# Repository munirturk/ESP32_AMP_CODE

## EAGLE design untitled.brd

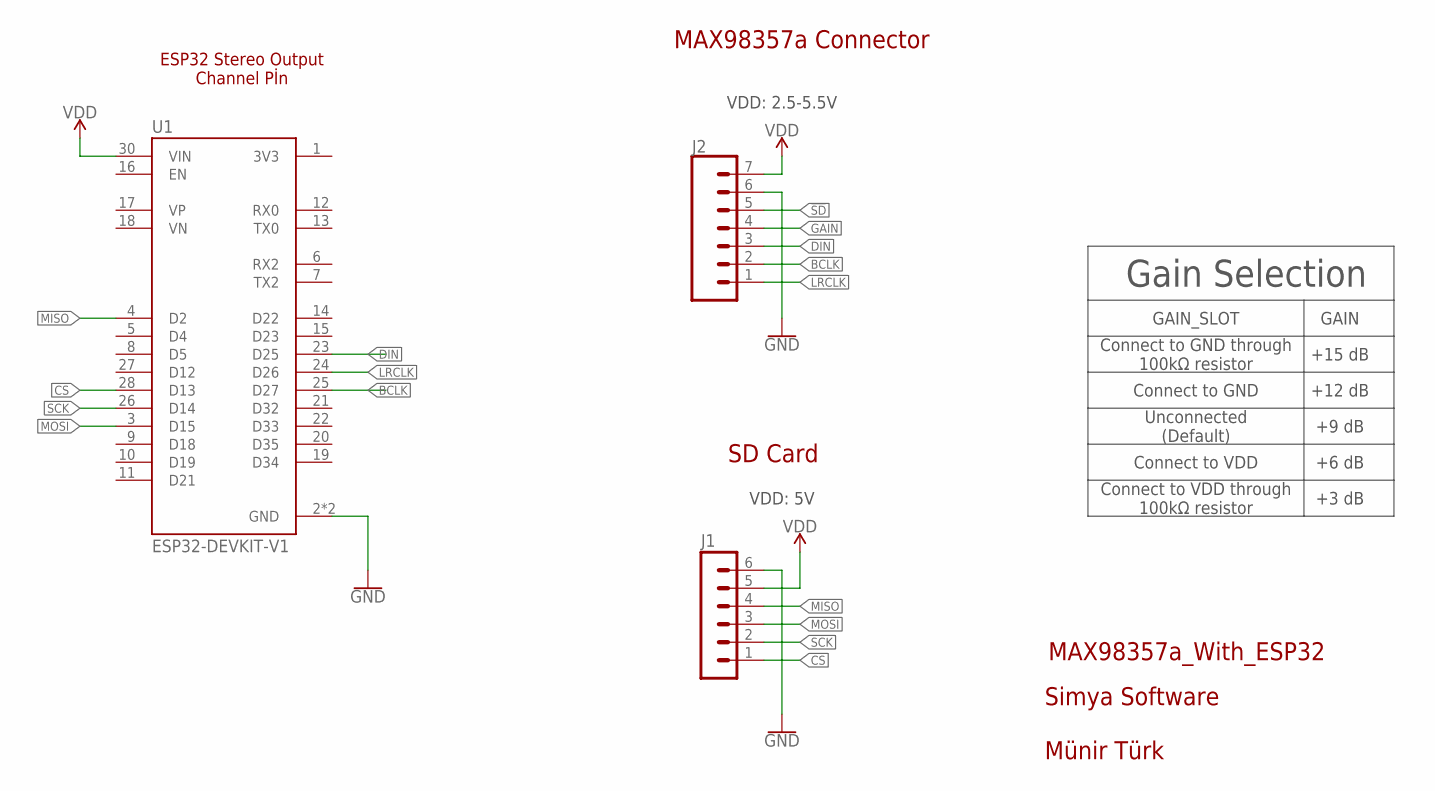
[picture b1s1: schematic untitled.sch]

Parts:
J1: MA06-1
J2: CONN_07NO_SILK; 1X07_NO_SILK
U1: ESP32-DEVKIT-V1; MODULE_ESP32_DEVKIT_V1

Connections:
!SD: J2.5
BCLK: J2.2, U1.25 (D27)
CS: J1.1, U1.28 (D13)
DIN: J2.3, U1.23 (D25)
GAIN: J2.4
GND: J1.6, J2.6, U1.2 (GND), U1.29 (GND)
LRCLK: J2.1, U1.24 (D26)
MISO: J1.4, U1.4 (D2)
MOSI: J1.3, U1.3 (D15)
SCK: J1.2, U1.26 (D14)
VDD: J1.5, J2.7, U1.30 (VIN)

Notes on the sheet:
Münir Türk
MAX98357a Connector
ESP32 Stereo Output Channel Pİn
Gain Selection
Connect to GND through 100kΩ resistor
Connect to GND
Unconnected (Default)
Connect to VDD
Connect to VDD through 100kΩ resistor
+15 dB
+12 dB
+9 dB
+6 dB
+3 dB
GAIN_SLOT
GAIN
VDD: 2.5-5.5V
SD Card
VDD: 5V
MAX98357a_With_ESP32
Simya Software

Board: 2 copper layers, 5 parts (0 on the bottom side), 9 nets, no tracks yet.

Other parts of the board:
H3, H4: STAND-OFF

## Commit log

2022-04-14 Create code

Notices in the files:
parts and their libraries:
SparkFun-Hardware: Licensing: Creative Commons ShareAlike 4.0 International - https://creativecommons.org/licenses/by-sa/4.0
